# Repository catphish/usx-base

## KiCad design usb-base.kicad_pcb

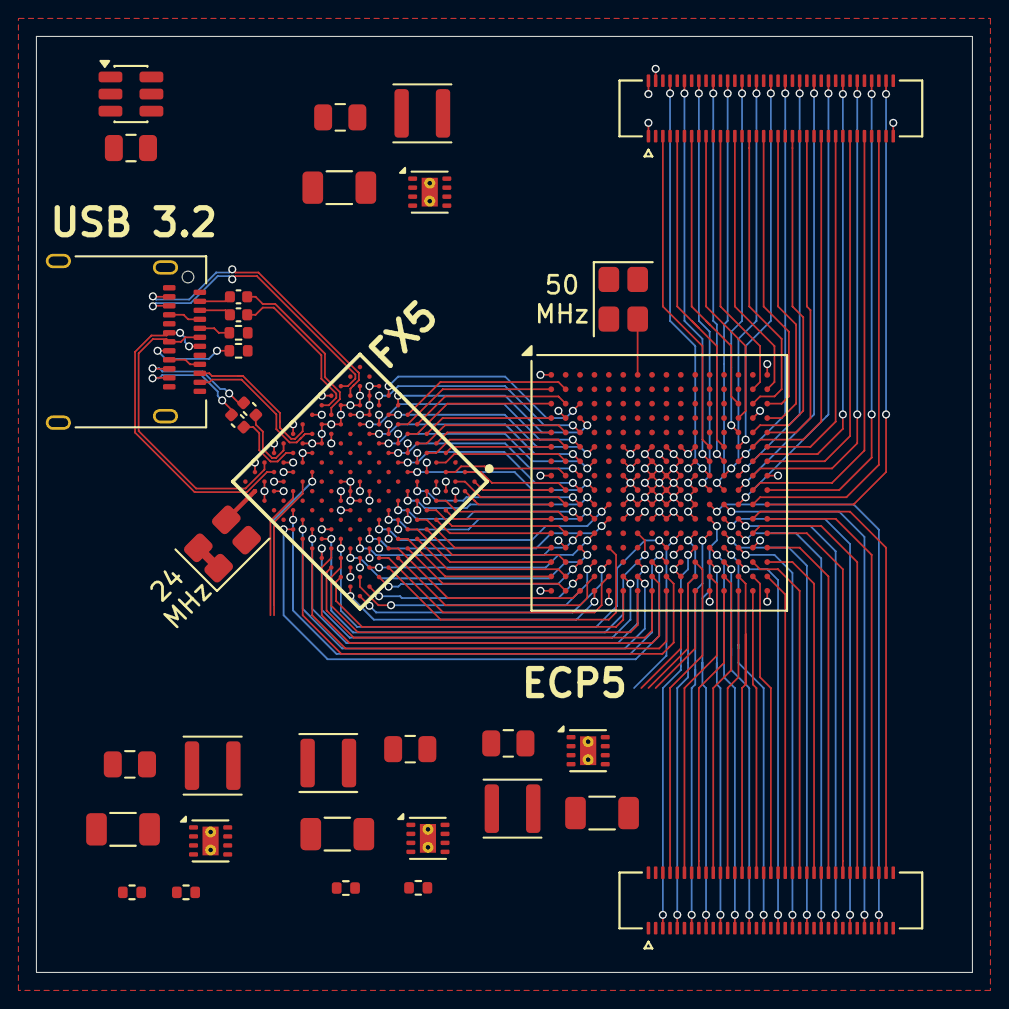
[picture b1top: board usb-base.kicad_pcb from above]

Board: 6 copper layers, 52.0 x 52.0 mm, 35 parts (0 on the bottom side), 165 nets.

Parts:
C1, C6, C9, C10, C14: 10u; C_0805_2012Metric
C2, C5, C11, C15: 22u; C_1206_3216Metric
C7, C8, C12, C13: 100n; C_0402_1005Metric
J1, J2: Conn_02x35_Odd_Even; Hirose_DF40C-70DS-0.4V_2x35_P0.4mm
J3: USB_C_Receptacle; USB_C_Receptacle_Amphenol_12401610E4-2A
L1, L2, L3, L4: 2.2u; L_Sunlord_SWPA3015S
R4: 20k; R_0402_1005Metric
R5: 7.5k; R_0402_1005Metric
R6, R7, R8, R9: R; R_0402_1005Metric
U1: CYUSB3082-FCAXI; BGA169N075P13X13_10X10X120
U2: TPS25221; SOT-23-6
U3: TPS62161DSG; WSON-8-1EP_2x2mm_P0.5mm_EP0.9x1.6mm_ThermalVias
U4: LFE5U-25F-6BG256C; BGA-256_14.0x14.0mm_Layout16x16_P0.8mm_Ball0.45mm_Pad0.32mm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
U5, U8: TPS62160DSG; WSON-8-1EP_2x2mm_P0.5mm_EP0.9x1.6mm_ThermalVias
U6: TPS62162DSG; WSON-8-1EP_2x2mm_P0.5mm_EP0.9x1.6mm_ThermalVias
Y1: 24MHz; Crystal_SMD_SeikoEpson_TSX3225-4Pin_3.2x2.5mm
Y2: 50MHz; Crystal_SMD_SeikoEpson_TSX3225-4Pin_3.2x2.5mm

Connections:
2.5V: C15.1, L4.2, R6.1, U8.6 (VOS)
24MHZ: U1.M13 (P5_1_XTALOUT), Y1.3 (OUT)
50MHz: U4.A7 (PT38A/+/PCLKT0_0), Y2.3 (OUT)
+1.8V: C2.1, L2.2, U1.F9 (VDDD), U1.L3 (USB3V18), U1.L5 (USB3V18), U1.L7 (USB3V18), U1.L11 (VDDD), U1.M2 (USB3V18), U1.M4 (USB3V18), U1.M6 (USB3V18), U1.M8 (USB3V18), U1.M10 (VDDD), U3.6 (VOS)
+1V1: C11.1, L3.2, R5.1, U4.G6 (VCC[6]), U4.G7 (VCC[6]), U4.G9 (VCC[6]), U4.L8 (VCC[6]), U4.L9 (VCC[6]), U4.L10 (VCC[6]), U5.6 (VOS)
+2.5V: U4.G11 (VCCAUX[2]), U4.L7 (VCCAUX[2])
+3.3V: C5.1, J1.1, J1.2, J1.4, J1.69, J2.1, J2.2, J2.4, L1.2, U1.A3 (V33), U1.C3 (VDDIO_P0), U1.C5 (VDDIO_P1), U1.C7 (VDDIO_P1_CTRL), U1.C9 (VDDIO_P1), U1.C11 (VDDIO_QSPI), U1.E3 (VDDIO_P0_CTRL), U1.F7 (VDDIO), U1.G3 (VDDIO_P0), U1.J3 (V33), U1.L10 (V33), U1.L13 (VDDIO), U1.M12 (VDDIO_XTAL), U4.F6 (VCCIO0[2]), U4.F7 (VCCIO0[2]), U4.F10 (VCCIO1[2]), U4.F11 (VCCIO1[2]), U4.H6 (VCCIO7[2]), U4.H7 (VCCIO7[2]), U4.H11 (VCCIO2[2]), U4.J6 (VCCIO6[2]), U4.J7 (VCCIO6[2]), U4.J11 (VCCIO2[2]), U4.K11 (VCCIO3[2]), U4.L6 (VCCIO8), U4.L11 (VCCIO3[2]), U4.N10 (CFG_0), U6.6 (VOS), Y1.1 (~ST), Y1.4 (VCC), Y2.1 (~ST), Y2.4 (VCC)
+5V: C1.1, C6.1, C9.1, C10.1, C14.1, U2.6 (OUT), U3.2 (VIN), U3.3 (EN), U5.2 (VIN), U5.3 (EN), U6.2 (VIN), U6.3 (EN), U8.2 (VIN), U8.3 (EN)
/TX1+: C8.1, J3.A2 (TX1+)
/TX1-: C7.1, J3.A3 (TX1-)
/TX2+: C13.1, J3.B2 (TX2+)
/TX2-: C12.1, J3.B3 (TX2-)
D0_0: J1.5, U4.F12 (PR17D/-/RDQ17)
D0_1: J1.8, U4.H12 (PR26A/+/HS/RDQ29)
D0_2: J1.9, U4.F13 (PR17C/+/RDQ17)
D0_3: J1.12, U4.G12 (PR20A/+/HS/RDQ17)
D0_4: J1.13, U4.C14 (PR11C/+/RDQ17)
D0_5: J1.16, U4.J12 (PR26D/-/RDQ29)
D0_6: J1.17, U4.D14 (PR11D/-/RDQ17)
D0_7: J1.20, U4.G13 (PR20B/-/HS/RDQ17)
D0_8: J1.21, U4.B15 (PR11B/-/URC_GPLL0C_IN/HS/RDQ17)
D0_9: J1.24, U4.J13 (PR26C/+/RDQ29)
D0_10: J1.25, U4.B16 (PR11A/+/URC_GPLL0T_IN/HS/RDQ17)
D0_11: J1.28, U4.E14 (PR14C/+/RDQ17)
D0_12: J1.29, U4.C15 (PR14B/-/HS/RDQ17)
D0_13: J1.32, U4.H13 (PR26B/-/HS/RDQ29)
D0_14: J1.33, U4.C16 (PR14A/+/HS/RDQ17)
D0_15: J1.36, U4.F14 (PR14D/-/RDQ17)
D0_16: J1.37, U4.D16 (PR17A/+/HS/RDQS17)
D0_17: J1.40, U4.G14 (PR23C/+/VREF1_2/RDQ29)
D0_18: J1.41, U4.E15 (PR17B/-/HS/RDQSN17)
D0_19: J1.44, U4.H14 (PR23D/-/RDQ29)
D0_20: J1.45, U4.E16 (PR20D/-/RDQ17)
D0_21: J1.48, U4.J14 (PR29C/+/GR_PCLK2_0/RDQ29)
D0_22: J1.49, U4.F15 (PR20C/+/RDQ17)
D0_23: J1.52, U4.K14 (PR29D/-/RDQ29)
D0_24: J1.53, U4.F16 (PR23A/+/HS/RDQ29)
D0_25: J1.56, U4.G15 (PR23B/-/HS/RDQ29)
D0_26: J1.57, U4.G16 (PR29A/+/GR_PCLK2_1/HS/RDQS29)
D0_27: J1.60, U4.H15 (PR29B/-/HS/RDQSN29)
D0_28: J1.61, U4.J15 (PR32B/-/PCLKC2_1/HS/RDQ29)
D0_29: J1.64, U4.J16 (PR32A/+/PCLKT2_1/HS/RDQ29)
D0_30: J1.65, U4.K15 (PR32D/-/PCLKC2_0/RDQ29)
D0_31: J1.68, U4.K16 (PR32C/+/PCLKT2_0/RDQ29)
D1_0: J2.5, U4.N11 (PR68B/-/HS/RDQ65)
D1_1: J2.8, U4.P11 (PR68C/+/LRC_GPLL0T_IN/RDQ65)
D1_2: J2.9, U4.M11 (PR68A/+/HS/RDQ65)
D1_3: J2.12, U4.R12 (PR65A/+/HS/RDQS65)
D1_4: J2.13, U4.M12 (PR65C/+/RDQ65)
D1_5: J2.16, U4.T13 (PR65B/-/HS/RDQSN65)
D1_6: J2.17, U4.L12 (PR38D/-/RDQ41)
D1_7: J2.20, U4.R13 (PR62C/+/RDQ65)
D1_8: J2.21, U4.P12 (PR68D/-/LRC_GPLL0C_IN/RDQ65)
D1_9: J2.24, U4.T14 (PR62D/-/RDQ65)
D1_10: J2.25, U4.N12 (PR65D/-/RDQ65)
D1_11: J2.28, U4.R14 (PR62B/-/HS/RDQ65)
D1_12: J2.29, U4.P13 (PR62A/+/HS/RDQ65)
D1_13: J2.32, U4.T15 (PR59D/-/RDQ65)
D1_14: J2.33, U4.N13 (PR59A/+/HS/RDQ65)
D1_15: J2.36, U4.R15 (PR59C/+/RDQ65)
D1_16: J2.37, U4.P14 (PR59B/-/HS/RDQ65)
D1_17: J2.40, U4.R16 (PR44B/-/VREF1_3/HS/RDQ41)
D1_18: J2.41, U4.N14 (PR44D/-/RDQ41)
D1_19: J2.44, U4.P15 (PR41B/-/HS/RDQSN41)
D1_20: J2.45, U4.M13 (PR44C/+/RDQ41)
D1_21: J2.48, U4.P16 (PR44A/+/HS/RDQ41)
D1_22: J2.49, U4.M14 (PR41D/-/RDQ41)
D1_23: J2.52, U4.N16 (PR41A/+/HS/RDQS41)
D1_24: J2.53, U4.L14 (PR41C/+/RDQ41)
D1_25: J2.56, U4.M16 (PR35C/+/PCLKT3_0/RDQ41)
D1_26: J2.57, U4.L13 (PR38C/+/GR_PCLK3_1/RDQ41)
D1_27: J2.60, U4.M15 (PR35D/-/PCLKC3_0/RDQ41)
D1_28: J2.61, U4.K13 (PR38A/+/GR_PCLK3_0/HS/RDQ41)
D1_29: J2.64, U4.L16 (PR35A/+/PCLKT3_1/HS/RDQ41)
D1_30: J2.65, U4.K12 (PR38B/-/HS/RDQ41)
D1_31: J2.68, U4.L15 (PR35B/-/PCLKC3_1/HS/RDQ41)
DONE: U1.J12 (P9_7_I2S0-RXMCLK), U4.P9 (DONE)
GND: C1.2, C2.2, C5.2, C6.2, C9.2, C10.2, C11.2, C14.2, C15.2, J1.3, J1.6, J1.7, J1.10, J1.11, J1.14, J1.15, J1.18, J1.19, J1.22, J1.23, J1.26, J1.27, J1.30, J1.31, J1.34, J1.35, J1.38, J1.39, J1.42, J1.43, J1.46, J1.47, J1.50, J1.51, J1.54, J1.55, J1.58, J1.59, J1.62, J1.63, J1.66, J1.67, J1.70, J2.3, J2.6, J2.7, J2.10, J2.11, J2.14, J2.15, J2.18, J2.19, J2.22, J2.23, J2.26, J2.27, J2.30, J2.31, J2.34, J2.35, J2.38, J2.39, J2.42, J2.43, J2.46, J2.47, J2.50, J2.51, J2.54, J2.55, J2.58, J2.59, J2.62, J2.63, J2.66, J2.67, J2.69, J2.70, J3.A1 (GND), J3.A12 (GND), J3.B1 (GND), J3.B12 (GND), J3.SH (SHIELD), R4.2, R7.2, R8.1, R9.1, U1.B3 (VSS), U1.C4 (VSS), U1.C6 (VSS), U1.C8 (VSS), U1.C10 (VSS), U1.C12 (VSS), U1.D3 (VSS), U1.F3 (VSS), U1.F8 (VSS), U1.G8 (VSS), U1.H3 (VSS), U1.H8 (VSS), U1.K3 (VSS), U1.L1 (VSS), U1.L2 (VSS), U1.L4 (VSS), U1.L6 (VSS), U1.L8 (VSS), U1.L9 (VSS), U1.L12 (VSS), U1.N2 (VSS), U1.N4 (VSS), U1.N6 (VSS), U1.N8 (VSS), U1.N10 (VSS), U1.N12 (VSS), U2.2 (GND), U3.1 (PGND), U3.4 (AGND), U3.5 (FB), U3.9 (PAD), U4.A1 (GND[27]), U4.A16 (GND[27]), U4.D2 (GND[27]), U4.D15 (GND[27]), U4.F8 (GND[27]), U4.F9 (GND[27]), U4.G8 (GND[27]), U4.G10 (GND[27]), U4.H1 (GND[27]), U4.H8 (GND[27]), U4.H9 (GND[27]), U4.H10 (GND[27]), U4.H16 (GND[27]), U4.J8 (GND[27]), U4.J9 (GND[27]), U4.J10 (GND[27]), U4.K6 (GND[27]), U4.K7 (GND[27]), U4.K8 (GND[27]), U4.K9 (GND[27]), U4.K10 (GND[27]), U4.N2 (GND[27]), U4.N15 (GND[27]), U4.P10 (CFG_1), U4.R10 (CFG_2), U4.T1 (GND[27]), U4.T5 (GND[27]), U4.T12 (GND[27]), U4.T16 (GND[27]), U5.1 (PGND), U5.4 (AGND), U5.9 (PAD), U6.1 (PGND), U6.4 (AGND), U6.5 (FB), U6.9 (PAD), U8.1 (PGND), U8.4 (AGND), U8.9 (PAD), Y1.2 (GND), Y2.2 (GND)
GPIO_0: U1.C13 (P6_4_SPICS3), U4.T6 (PB4A/+/D7/IO7)
GPIO_1: U1.H13 (P0_0_P0SDA), U4.P8 (PB13B/-/CS1N)
GPIO_2: U1.F12 (P13_1_GPIO4), U4.M7 (PB9B/-/D2/IO2)
GPIO_3: U1.H12 (P10_0_I2C-SCL0), U4.R7 (PB6A/+/D5/MISO2/IO5)
GPIO_4: U1.G12 (P10_1_I2C-SDA0), U4.P7 (PB6B/-/D4/MOSI2/IO4)
GPIO_5: U1.E13 (P8_7_P1SCL), U4.R6 (PB4B/-/D6/IO6)
INITN: U1.F13 (P8_6_P1SDA), U4.T9 (INITN)
unnamed: U1.G7 (VCCD), U1.G9 (VCCD)
unnamed: J3.A5 (CC1), R9.2
unnamed: J3.B5 (CC2), R8.2
unnamed: L2.1, U3.7 (SW)
unnamed: R4.1, R5.2, U5.5 (FB)
unnamed: L3.1, U5.7 (SW)
unnamed: L1.1, U6.7 (SW)
unnamed: R6.2, R7.1, U8.5 (FB)
unnamed: L4.1, U8.7 (SW)
P0CLK: U1.A1 (P0CLK/P0CTL8), U4.J1 (PL32A/+/PCLKT7_1/HS/LDQ29)
P0CTL0: U1.K4 (P0CTL0), U4.F3 (PL14D/-/LDQ17)
P0CTL1: U1.J4 (P0CTL1), U4.G3 (PL23C/+/VREF1_7/LDQ29)
P0CTL2: U1.H4 (P0CTL2), U4.G4 (PL20B/-/HS/LDQ17)
P0CTL3: U1.G4 (P0CTL3), U4.H3 (PL23D/-/LDQ29)
P0CTL4: U1.F4 (P0CTL4), U4.J3 (PL29C/+/GR_PCLK7_0/LDQ29)
P0CTL5: U1.E4 (P0CTL5), U4.J4 (PL26C/+/LDQ29)
P0CTL6: U1.D4 (P0CTL6), U4.K3 (PL29D/-/LDQ29)
P0CTL7: U1.F2 (P0CTL7), U4.E2 (PL17B/-/HS/LDQSN17)
P0CTL8: U1.J1 (P0CTL8/P0D9), U4.D3 (PL11D/-/LDQ17)
P0CTL9: U1.A2 (P0CTL9), U4.K1 (PL32C/+/PCLKT7_0/LDQ29)
P0D0: U1.K2 (P0D0), U4.E3 (PL14C/+/LDQ17)
P0D1: U1.J2 (P0D1), U4.F4 (PL17C/+/LDQ17)
P0D2: U1.H2 (P0D2), U4.B1 (PL11A/+/ULC_GPLL0T_IN/HS/LDQ17)
P0D3: U1.G2 (P0D3), U4.C1 (PL14A/+/HS/LDQ17)
P0D4: U1.E2 (P0D4), U4.F2 (PL20C/+/LDQ17)
P0D5: U1.D2 (P0D5), U4.G2 (PL23B/-/HS/LDQ29)
P0D6: U1.C2 (P0D6), U4.H2 (PL29B/-/HS/LDQSN29)
P0D7: U1.B2 (P0D7), U4.K2 (PL32D/-/PCLKC7_0/LDQ29)
P0D8: U1.K1 (P0D8), U4.C3 (PL11C/+/LDQ17)
P0D9: U1.F1 (P0D9/P0CLK), U4.D1 (PL17A/+/HS/LDQS17)
P0D10: U1.H1 (P0D10), U4.B2 (PL11B/-/ULC_GPLL0C_IN/HS/LDQ17)
P0D11: U1.G1 (P0D11), U4.C2 (PL14B/-/HS/LDQ17)
P0D12: U1.E1 (P0D12), U4.E1 (PL20D/-/LDQ17)
P0D13: U1.D1 (P0D13), U4.F1 (PL23A/+/HS/LDQ29)
P0D14: U1.C1 (P0D14), U4.G1 (PL29A/+/GR_PCLK7_1/HS/LDQS29)
P0D15: U1.B1 (P0D15), U4.J2 (PL32B/-/PCLKC7_1/HS/LDQ29)
P1CLK: U1.A5 (P1CLK/P1D9), U4.M1 (PL35C/+/PCLKT6_0/LDQ41)
P1CTL0: U1.D5 (P1CTL0), U4.K4 (PL38A/+/GR_PCLK6_0/HS/LDQ41)
P1CTL1: U1.D6 (P1CTL1), U4.L3 (PL41C/+/LDQ41)
P1CTL2: U1.D7 (P1CTL2), U4.L4 (PL38C/+/GR_PCLK6_1/LDQ41)
P1CTL3: U1.D8 (P1CTL3), U4.K5 (PL38B/-/HS/LDQ41)
P1CTL4: U1.D9 (P1CTL4), U4.L5 (PL38D/-/LDQ41)
P1CTL5: U1.D10 (P1CTL5), U4.M3 (PL41D/-/LDQ41)
P1CTL6: U1.D11 (P1CTL6), U4.N3 (PL44D/-/LDQ41)
P1CTL7: U1.B8 (P1CTL7), U4.R1 (PL44B/-/VREF1_6/HS/LDQ41)
P1CTL8: U1.A13 (P1CTL8), U4.P5 (PL68D/-/LLC_GPLL0C_IN/LDQ65)
P1CTL9: U1.B13 (P1CTL9), U4.T4 (PL65B/-/HS/LDQSN65)
P1D0: U1.B4 (P1D0), U4.L2 (PL35B/-/PCLKC6_1/HS/LDQ41)
P1D1: U1.B5 (P1D1), U4.M2 (PL35D/-/PCLKC6_0/LDQ41)
P1D2: U1.B6 (P1D2), U4.N1 (PL41A/+/HS/LDQS41)
P1D3: U1.B7 (P1D3), U4.P1 (PL44A/+/HS/LDQ41)
P1D4: U1.B9 (P1D4), U4.T3 (PL62D/-/LDQ65)
P1D5: U1.B10 (P1D5), U4.R5 (PL65A/+/HS/LDQS65)
P1D6: U1.B11 (P1D6), U4.M4 (PL44C/+/LDQ41)
P1D7: U1.B12 (P1D7), U4.P4 (PL62A/+/HS/LDQ65)
P1D8: U1.A4 (P1D8), U4.L1 (PL35A/+/PCLKT6_1/HS/LDQ41)
P1D9: U1.A8 (P1D9/P1CLK), U4.T2 (PL59D/-/LDQ65)
P1D10: U1.A6 (P1D10), U4.P2 (PL41B/-/HS/LDQSN41)
P1D11: U1.A7 (P1D11), U4.R2 (PL59C/+/LDQ65)
P1D12: U1.A9 (P1D12), U4.R4 (PL62C/+/LDQ65)
P1D13: U1.A10 (P1D13), U4.N5 (PL65D/-/LDQ65)
P1D14: U1.A11 (P1D14), U4.P3 (PL59B/-/HS/LDQ65)
P1D15: U1.A12 (P1D15), U4.R3 (PL62B/-/HS/LDQ65)
PROGRAMN: U1.G13 (P0_1_P0SCL), U4.R9 (PROGRAMN)
SSPI_CLK: U1.E11 (P6_0_SPICLK), U4.N9 (CCLK/MCLK/SCK)
SSPI_CS: U1.E12 (P6_1_SPICS0), U4.R8 (PB13A/+/SN/CSN)
SSPI_MISO: U1.D12 (P6_3_SPICS2), U4.T7 (PB11A/+/D1/MISO/IO1)
SSPI_MOSI: U1.D13 (P6_2_SPICS1), U4.T8 (PB11B/-/D0/MOSI/IO0)
USBFS_D+: U1.M1 (USBFSD_N), U1.N1 (USBFSD_P)
USBHS_D+: J3.A6 (D+), J3.B6 (D+), U1.N11 (USBHSD_P)
USBHS_D-: J3.A7 (D-), J3.B7 (D-), U1.M11 (USBHSD_N)
USBSS_RX1+: J3.B11 (RX1+), U1.M3 (USB3RX1_P)
USBSS_RX1-: J3.B10 (RX1-), U1.N3 (USB3RX1_N)
USBSS_RX2+: J3.A11 (RX2+), U1.M7 (USB3TX2_P)
USBSS_RX2-: J3.A10 (RX2-), U1.N7 (USB3TX2_N)
USBSS_TX1+: C8.2, U1.M5 (USB3TX1_P)
USBSS_TX1-: C7.2, U1.N5 (USB3TX1_N)
USBSS_TX2+: C13.2, U1.M9 (USB3RX2_P)
USBSS_TX2-: C12.2, U1.N9 (USB3RX2_N)
VBUS_IN: J3.A4 (VBUS), J3.A9 (VBUS), J3.B4 (VBUS), J3.B9 (VBUS), U2.1 (IN), U2.3 (EN)

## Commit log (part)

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2026-06-09 Initial commit. Partial schematic and layout.
2026-06-10 Power supplies, oscillators, user IO breakout
2026-06-19 Remove DDR support in favour of cleaner bus routing
